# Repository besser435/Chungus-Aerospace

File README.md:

# Chungus-Aerospace
For the model rockets made by my friend and myself.
Most of the code was written before I knew how to code/keep it maintainable, which is why pretty much everything is terrible.

chung

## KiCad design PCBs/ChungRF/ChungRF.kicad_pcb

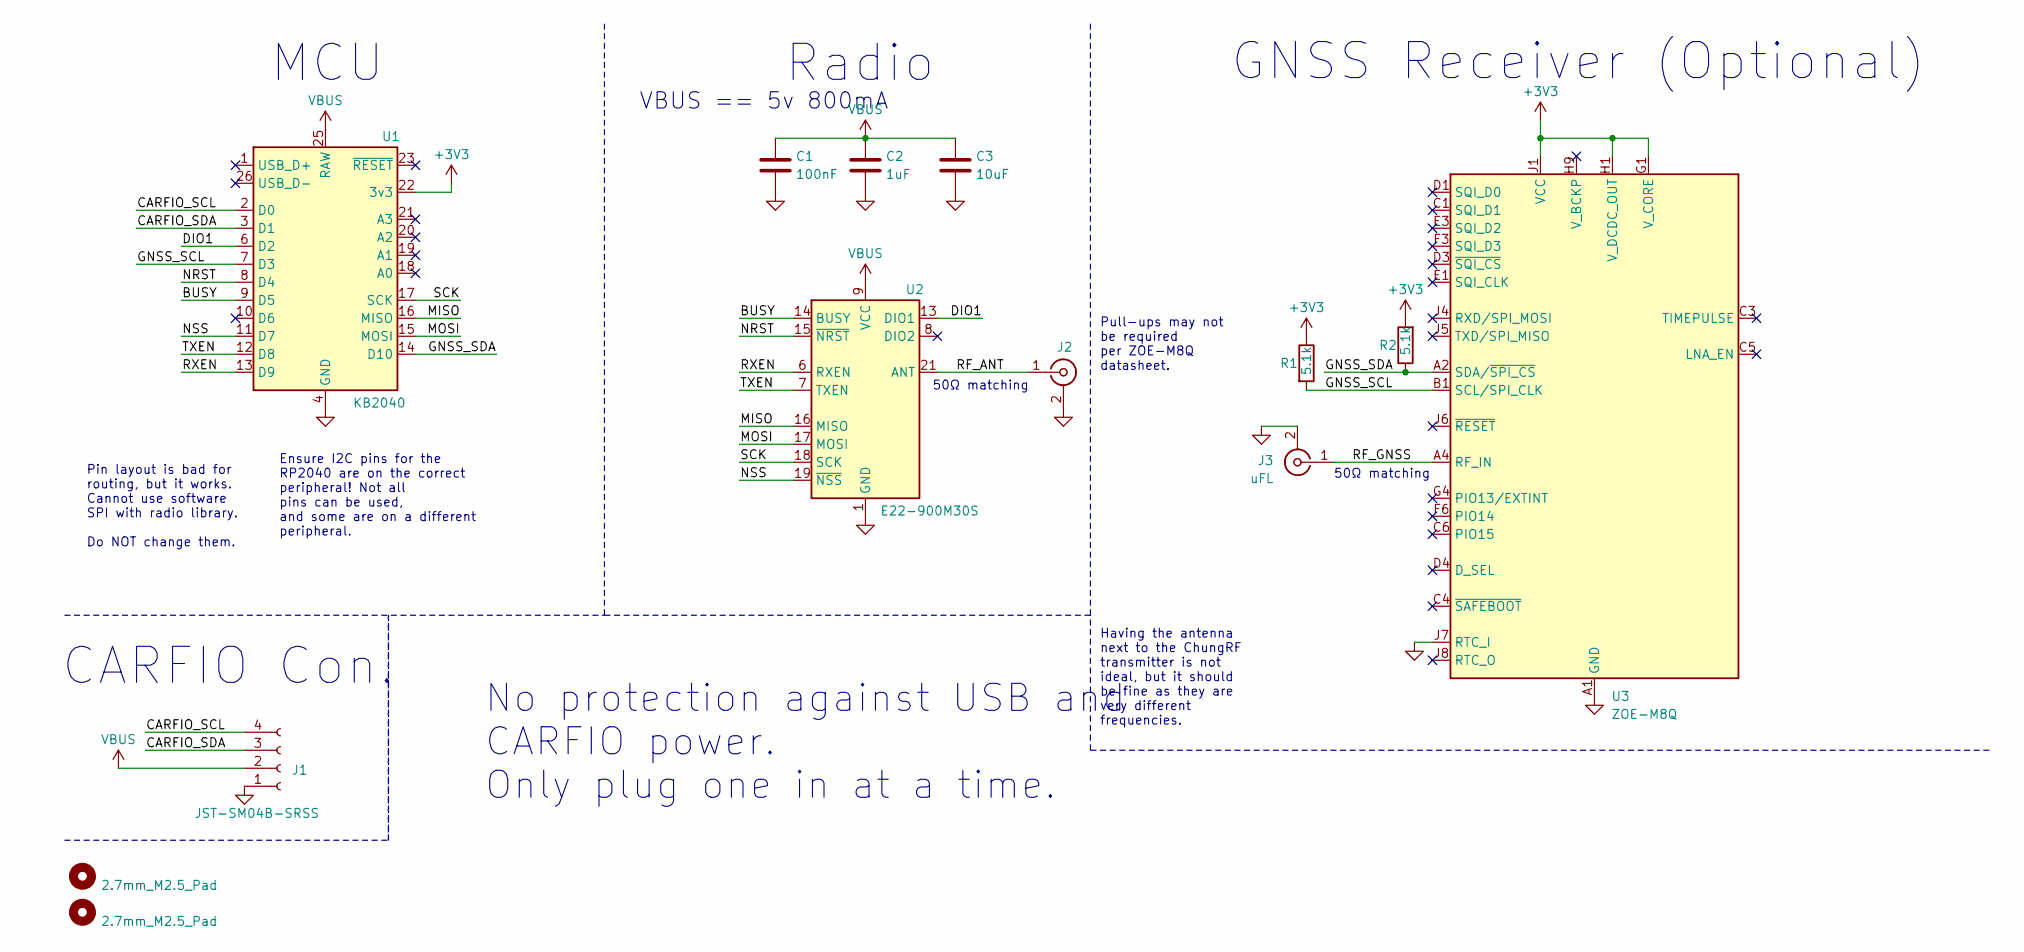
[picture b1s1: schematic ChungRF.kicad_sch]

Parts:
C1: 100nF; C_0603_1608Metric
C2: 1uF; C_0603_1608Metric
C3: 10uF; C_0603_1608Metric
H1, H2: 2.7mm_M2.5_Pad; M2.5_2.7mm_hole
J1: JST-SM04B-SRSS; JST_SH_SM04B-SRSS-TB_1x04-1MP_P1.00mm_Horizontal
J2: Conn_Coaxial; CONSMA003.062
J3: uFL; U.FL_Hirose_U.FL-R-SMT-1_Vertical
R1, R2: 5.1k; C_0603_1608Metric
U1: KB2040; Adafuit-KB2040-SMD
U2: E22-900M30S
U3: ZOE-M8Q; ublox_ZOE_M8

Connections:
+3V3: R1.1, R2.2, U1.22 (3v3), U3.G1 (V_CORE), U3.H1 (V_DCDC_OUT), U3.J1 (VCC), U3.J2 (VCC)
/BUSY: U1.9 (D5), U2.14 (BUSY)
/CARFIO_SCL: J1.4, U1.2 (D0)
/CARFIO_SDA: J1.3, U1.3 (D1)
/DIO1: U1.6 (D2), U2.13 (DIO1)
/GNSS_SCL: R1.2, U1.7 (D3), U3.B1 (SCL/SPI_CLK)
/GNSS_SDA: R2.1, U1.14 (D10), U3.A2 (SDA/~SPI_CS)
/MISO: U1.16 (MISO), U2.16 (MISO)
/MOSI: U1.15 (MOSI), U2.17 (MOSI)
/NRST: U1.8 (D4), U2.15 (~NRST)
/NSS: U1.11 (D7), U2.19 (~NSS)
/RF_ANT: J2.1 (In), U2.21 (ANT)
/RF_GNSS: J3.1 (In), U3.A4 (RF_IN)
/RXEN: U1.13 (D9), U2.6 (RXEN)
/SCK: U1.17 (SCK), U2.18 (SCK)
/TXEN: U1.12 (D8), U2.7 (TXEN)
GND: C1.2, C2.2, C3.2, J1.1, J2.2 (Ext), J3.2 (Ext), U1.4 (GND), U1.5 (GND), U1.24 (GND), U2.1 (GND), U2.2 (GND), U2.3 (GND), U2.4 (GND), U2.5 (GND), U2.11 (GND), U2.12 (GND), U2.20 (GND), U2.22 (GND), U3.A1 (GND), U3.A3 (GND), U3.A5 (GND), U3.A7 (GND), U3.A8 (GND), U3.A9 (GND), U3.B9 (GND), U3.C7 (GND), U3.C9 (GND), U3.D6 (GND), U3.D9 (GND), U3.E7 (GND), U3.F7 (GND), U3.G3 (GND), U3.G6 (GND), U3.G7 (GND), U3.J3 (GND), U3.J7 (RTC_I), U3.J9 (GND)
VBUS: C1.1, C2.1, C3.1, J1.2, U1.25 (RAW), U2.9 (VCC), U2.10 (VCC)

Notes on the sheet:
VBUS == 5v 800mA
Radio
No protection against USB and CARFIO power. Only plug one in at a time.
Having the antenna next to the ChungRF transmitter is not ideal, but it should be fine as they are very different frequencies.
MCU
CARFIO Con.
Pull-ups may not be required per ZOE-M8Q datasheet.
Ensure I2C pins for the RP2040 are on the correct peripheral! Not all pins can be used, and some are on a different peripheral.
Pin layout is bad for routing, but it works. Cannot use software SPI with radio library. Do NOT change them.
50Ω matching
GNSS Receiver (Optional)

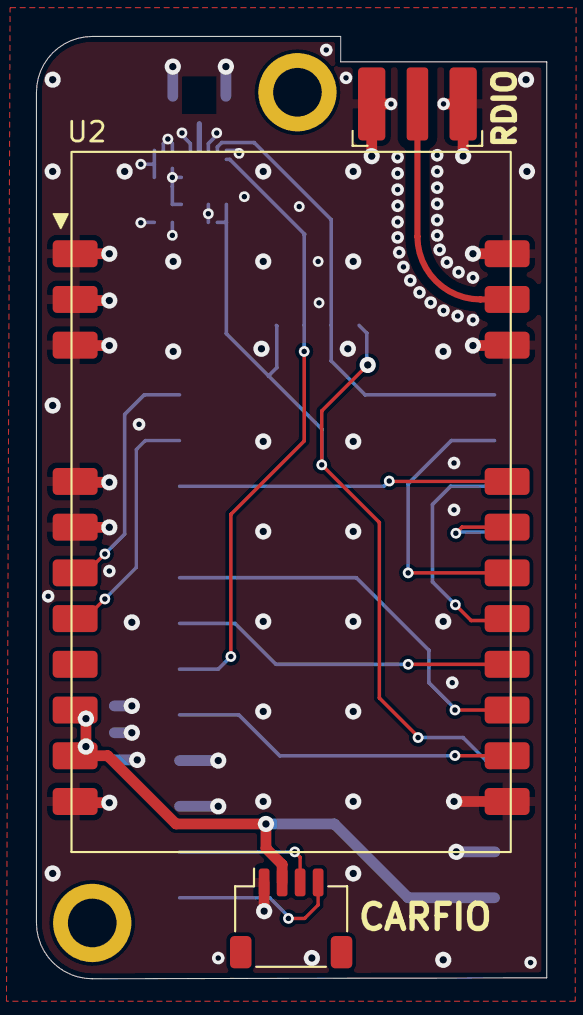
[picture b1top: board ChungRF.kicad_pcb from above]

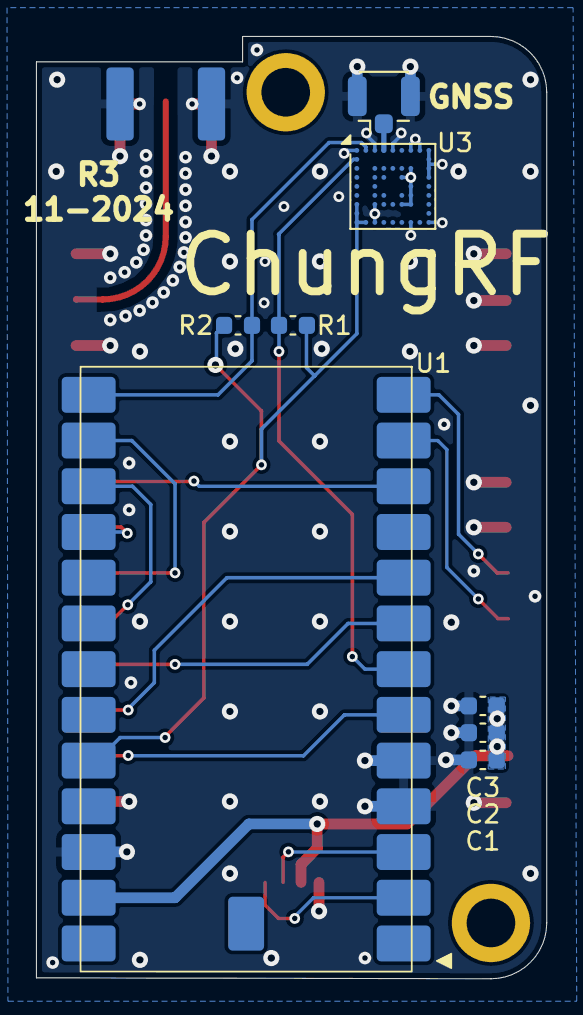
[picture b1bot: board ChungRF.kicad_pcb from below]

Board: 4 copper layers, 28.3 x 52.3 mm, 13 parts (8 on the bottom side), 18 nets.

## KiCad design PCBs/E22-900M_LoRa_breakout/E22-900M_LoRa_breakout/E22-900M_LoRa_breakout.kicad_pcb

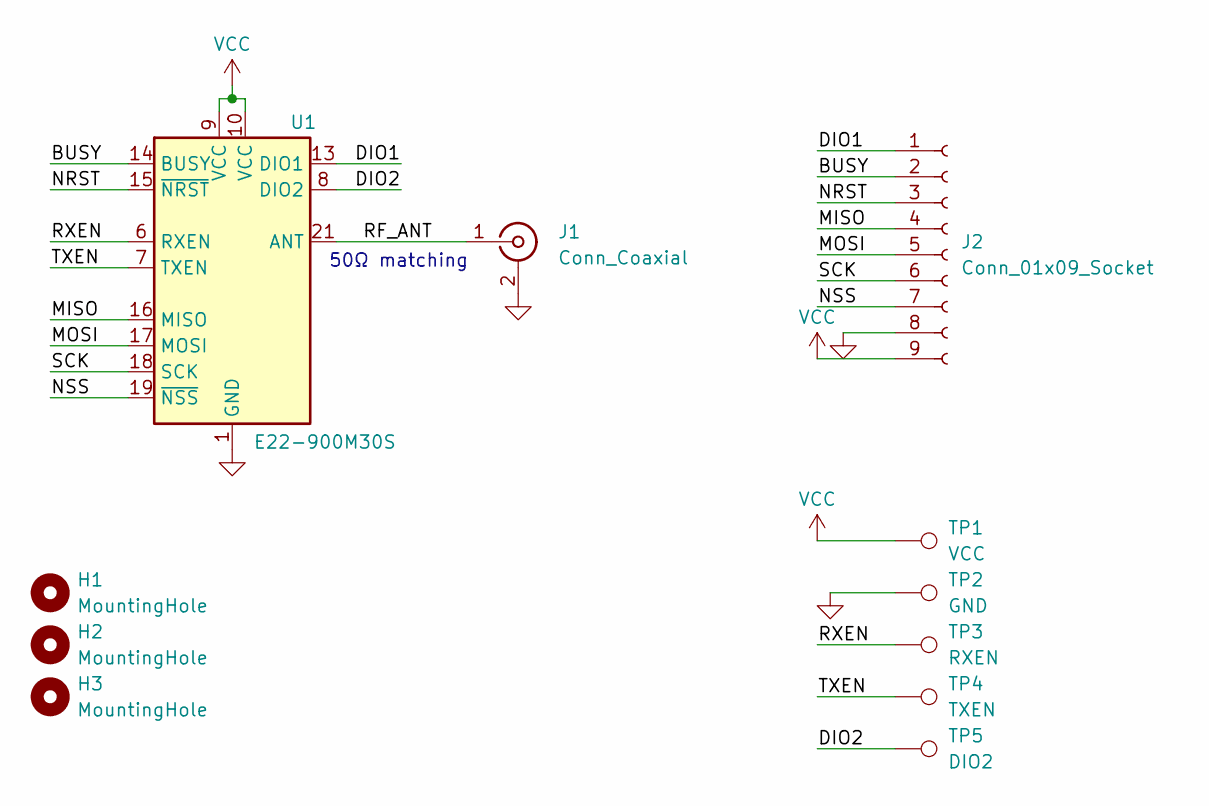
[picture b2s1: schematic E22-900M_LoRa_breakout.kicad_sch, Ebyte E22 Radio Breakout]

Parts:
H1, H2, H3: MountingHole; MountingHole_2.7mm_M2.5_Pad_Via
J1: Conn_Coaxial; CON-SMA-EDGE-S
J2: Conn_01x09_Socket; JST_GH_BM09B-GHS-TBT_1x09-1MP_P1.25mm_Vertical
TP1: VCC; TestPoint_Pad_D1.5mm
TP2: GND; TestPoint_Pad_D1.5mm
TP3: RXEN; TestPoint_Pad_D1.5mm
TP4: TXEN; TestPoint_Pad_D1.5mm
TP5: DIO2; TestPoint_Pad_D1.5mm
U1: E22-900M30S

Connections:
/BUSY: J2.2, U1.14 (BUSY)
/DIO1: J2.1, U1.13 (DIO1)
/DIO2: TP5.1, U1.8 (DIO2)
/MISO: J2.4, U1.16 (MISO)
/MOSI: J2.5, U1.17 (MOSI)
/NRST: J2.3, U1.15 (~NRST)
/NSS: J2.7, U1.19 (~NSS)
/RF_ANT: J1.1 (In), U1.21 (ANT)
/RXEN: TP3.1, U1.6 (RXEN)
/SCK: J2.6, U1.18 (SCK)
/TXEN: TP4.1, U1.7 (TXEN)
GND: J1.2 (Ext), J2.8, TP2.1, U1.1 (GND), U1.2 (GND), U1.3 (GND), U1.4 (GND), U1.5 (GND), U1.11 (GND), U1.12 (GND), U1.20 (GND), U1.22 (GND)
VCC: J2.9, TP1.1, U1.9 (VCC), U1.10 (VCC)

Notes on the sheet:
50Ω matching

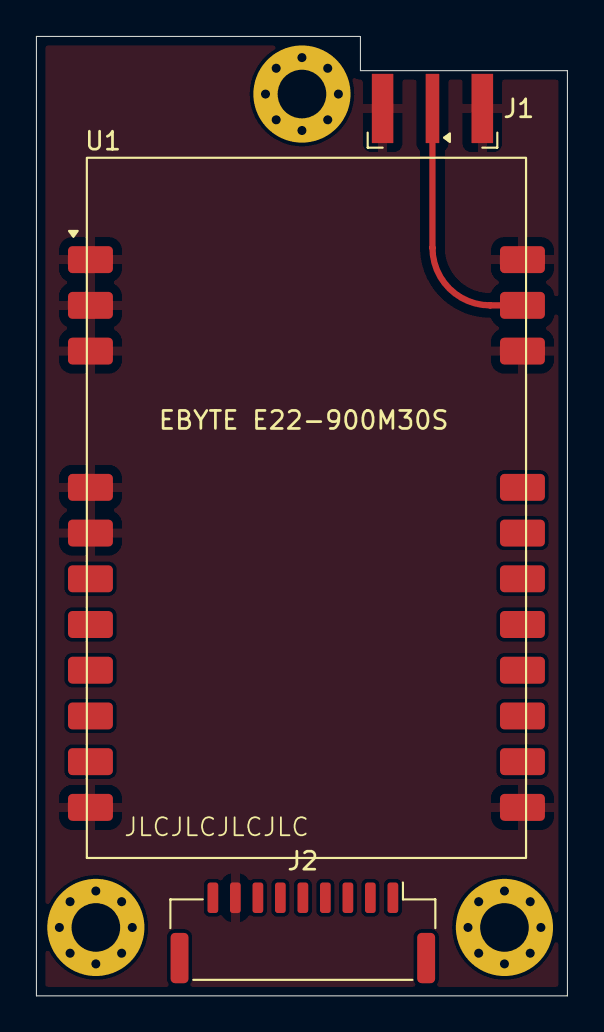
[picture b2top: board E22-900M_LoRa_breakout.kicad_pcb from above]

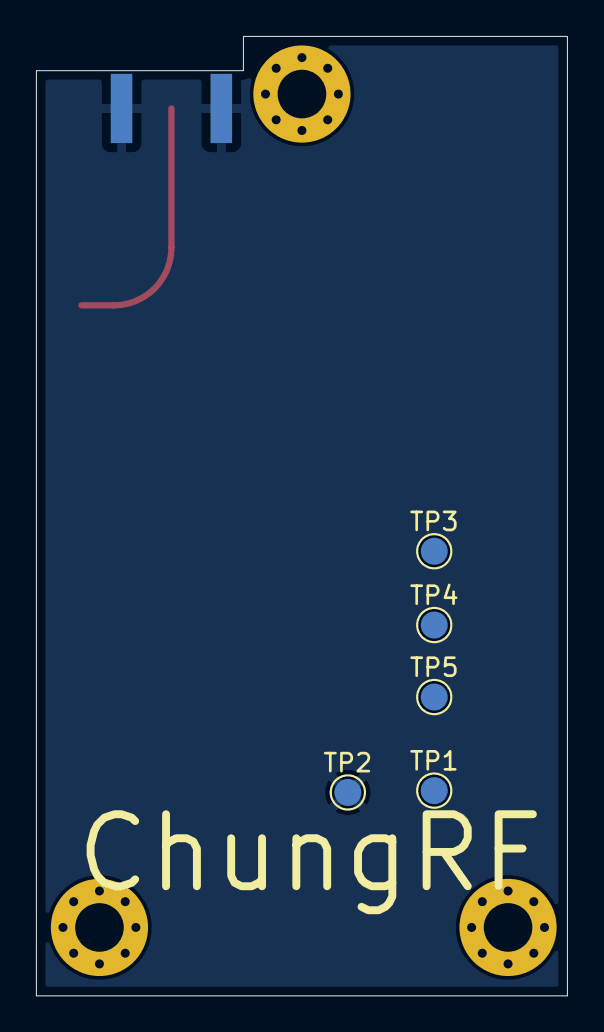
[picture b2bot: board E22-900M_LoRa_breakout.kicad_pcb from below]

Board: 4 copper layers, 29.5 x 53.3 mm, 11 parts (5 on the bottom side), 13 nets.

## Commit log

2021-12-29 chung
2021-12-29 v0.1
2021-12-31 v0.2
2021-12-31 borrowed project
    Hippity hoppity your code is now my property
2022-01-05 v0.2.1
    Added possible chute deploy code
2022-01-06 Added Feather Libraries
2022-01-06 v0.2.3
2022-01-08 v1.0
2022-01-09 v1.0.1
2022-01-12 v1.1
    debunged a few things
2022-01-12 legacy code
    This used to be required, but we changed how the code works. Because of this we don't need this bit anymore. I'm just uploading it incase we do need it again for whatever reason. We didn't write this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
2022-01-12 moved files
2022-01-12 Delete Feather-M4 Flight Telemetry Software.py
    Renamed to code.py so its easier to work with on the Feather.
2022-01-12 v1.2
2022-01-12 moved
2022-01-12 v1.3
2022-01-13 v1.1.1
2022-01-13 Our flight logs go here
2022-01-14 v1.1
2022-01-14 v1.4
2022-01-15 v1.5
2022-01-15 v0.1.1
2022-01-15 Why did I even make this
2022-01-16 1-15-22
2022-01-19 ooga booga
2022-01-19 v0.1.2
2022-01-19 test
2022-01-20 Committed to wrong part
2022-01-20 Name changes
2022-01-20 did the thing again
2022-01-20 File name change
2022-01-20 Updating files
2022-01-20 Clarified file names
2022-01-20 v1.6
2022-01-20 v0.1.3
2022-01-21 debugging logs for logging issue
2022-01-21 v1.7
2022-01-24 v1.8
2022-01-25 v1.8.1
2022-01-25 Updated directory structure
2022-01-25 Create why
2022-01-26 v1.9
2022-02-02 v2.2-alpha.1
2022-02-03 v2.0-alpha.2.3
    File and version name changes
2022-02-06 Adding untested MPIM parts
    Gotta make sure all the parts work together before committing to the main branch. Maybe even an operational flight.
2022-02-08 v1.10
2022-02-08 I will not make this a pull request
2022-02-09 Redoing RUD
2022-02-09 v2.0-alpha.3
2022-02-12 Updated tolerances a little
    It was wiggling around a little bit, so I made the tolerances a bit tighter to hopefully fix that.
2022-02-12 this part sucks lol
2022-02-16 v2.0-alpha.4
2022-02-17 CALC v2.0-alpha.5
2022-02-17 v1.10.2
2022-02-17 add CALCv1 mounts
2022-02-23 v1.11
2022-03-04 v2.0-alpha.6
2022-03-05 Moved MPIM stuff around, added 49mm MPIM
2022-03-14 v2.0-beta.1
2022-03-17 v1.12
2022-03-20 v2.0-beta.2
2022-03-22 v2.0-beta.3
2022-03-29 Not needed anymore
2022-04-06 v1.13
2022-04-06 v1.1.2
2022-04-08 v2.0-beta.4
2022-04-28 4-27-22
2022-05-04 init
2022-05-05 v2.0-beta.5
2022-05-15 More dual deployment parts
    Added a small 37.6x60mm avionics bay, bulkhead/coupler with space for wires and a pyro charge, 50mm long body tube for drogueless dual deployment, and a motor mount part that I forgot to add a while 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
2022-06-18 Transition to flyaway rod guide
    24x70mm only though, the 18mm ones are obsolete anyway
2022-07-05 updated lib
2022-07-06 flight
2022-07-14 Challenger ejection charge software v0.1
2022-07-21 First set of Full Send parts
2022-07-28 debung
2022-07-30 v1.2.1
2022-08-02 Updated Full Send
2022-08-20 v2.0-beta.6
2022-09-08 v1.14
2022-11-13 QT py velocity v0
    Now takes 30 seconds to reach FTL speeds instead of 3
    Also organized the clusterfuck of a QT py folder
2022-11-14 v1.1
    Made the code a bit neater
2022-11-14 v1.1 (#7)
    Made the code a bit neater
2022-11-20 Made integral less stupid
    Still untested, could very well be totally fucked, but it's definitely better than before
2022-11-20 Made variables less stupid and more readable
2022-11-21 defuck (#8)
    * Made integral less stupid
    * Made variables less stupid and more readable
2022-12-16 Fuller Send aerostructure
    .stl files and .csv file for the nose cone
2022-12-19 moved CALCv2
2022-12-25 v1.15-alpha.1
2022-12-25 Removed useless files
2022-12-25 Create code.py
    (Still untested, apparently I'm supposed to spend time with my family or something)
2022-12-30 Full accelerometer calibration, velocity logging
    I hate this
2022-12-31 Accelerometer calibration (#10)
    * Create code.py
    (Still untested, apparently I'm supposed to spend time with my family or something)
    * Full accelerometer calibration, velocity logging
    I hate this
    * Update code.py
    * Update code.py
2022-12-31 update file structure
2022-12-31 v1.15-beta.1
2022-12-31 v1.15
2023-01-03 v1.0-alpha.1
2023-03-01 Create Autism Ray PCB
2023-03-02 Update PCB
2023-03-02 Before ground pour
2023-03-02 Actaully before ground pour
2023-03-02 Actually after ground pour
2023-03-02 Update gitignore
2023-03-04 Update Eagle libraries
2023-03-09 Added XIAO lib
2023-03-15 Autosaves
2023-03-16 TF2 autosave
2023-03-17 Yagi hardware + calibration slight defuck
2023-03-19 Create thick parts
2023-03-19 v2.0-beta.7
2023-03-25 Tax Fraud v2 PCB
2023-03-25 Update autism_ray_xaio.b##
2023-04-12 Create TVC logic.py
    Needs more work. Idk how to reference specific elements in the array yet, but it's a start.
2023-04-13 TVC logic quat normalization + Euler
    Hopefully added code for normalizing the quaternion, and calculating one of the Euler angles. It should be possible to do a sanity check with this.
2023-04-14 TVC Euler math
    Finished Euler angle conversion math
2023-04-29 v1.0.2
    Rename to avoid linting errors in VS Code
2023-05-10 v1.0.3
2023-05-13 2020 rail/38mm launch tower parts
2023-05-14 Create BasicKalmanTest.py
    File for Kalman filter testing, no idea if it'll work
2023-05-28 v.1.1
2023-06-06 FS2 Avbay
2023-06-07 FS2 full avbay assembly
2023-06-08 FS2 avbay tolerance fix
    Defucked OD from 38.6mm to 38mm
2023-06-09 FS2 motor block
2023-06-29 FS2 motor blovck defuck i think
    I changed something maybe a week ago and forgot to commit lol
2023-06-29 FS2 29mm adapter
2023-07-01 TVC configuration
    something something conflicted file idk seems fine to me
2023-07-01 TVC configuration defuck
2023-07-02 Improved calibration
    Print formatting, gyro calibration, range defuck, renamed variables, kalman filter test that I completely forgot about
2023-07-02 stupid fucking radian conversion + format defuck
2023-07-06 7-6-23 launch
2023-07-11 Accelerometer velocity potential defuck
    Created cfg setup and new velocity logic that integrates first before getting the magnitude of the velocity vector.
2023-07-24 TVC logic setup (#11)
    * Create TVC logic.py
    Needs more work. Idk how to reference specific elements in the array yet, but it's a start.
    * TVC logic quat normalization + Euler
    Hopefully added code for normalizing the quaternion, and calculating one of the Euler angles. It should be possible to do a sanity check with this.
    * TVC Euler math
    Finished Euler angle conversion math
2023-07-24 TVC changes
2023-07-25 TVC array error possible defuck #2
2023-07-28 TVC/Accel logic defuck #3 (final)
    Modified TVC logic so it actually fucking works, cleaned it up and added comments so it's more readable, improved calibration, added PID constants to TVC config file for use in future features
2023-08-07 TVC body tube + nose cone generator
2023-09-15 TVC rocket body + QoL changes
    Updated TVC rocket body, changed frequency formula for autism ray ground software, unfucked nose cone generator math
2023-10-27 Rename, start landed function
2023-10-27 v1.3
    Add exit() in while True loop under keyboardInterrupt, fix HB text cutoff
2023-12-21 Remove old stuff
2024-01-26 v1.4: add display info, add cron job comment
2024-01-30 chunglib tvc 1
2024-01-30 FS2/TVC defuck?????
2024-01-30 chunglib tvc 1 (#12)
2024-02-03 Add UART test stuff
2024-02-07 Add initial AR2 tests
2024-02-14 Rev B - Fix UART pins
2024-02-14 Rev B - Improve ground plane
2024-02-14 Continue work on AR2
2024-02-16 git commit in case sussy house fire
    I am scared of data loss okay
2024-02-20 Update AR2 stuff
2024-02-23 AR2 updates
2024-03-04 Update AR2
2024-03-05 I am going insane
2024-03-07 Change out stupid fucking display library for an amazing one
2024-03-08 Update AR2, mostly functional now
2024-03-09 Change boot behavior, add alert display function
2024-03-20 Change fix quality to 3D indicator
2024-03-26 Blink on send to save power, add/fix comments
2024-04-04 Add power saving features, start on proper logging
2024-04-06 v1.2 - Reduce power by ~20mA
2024-04-06 v1.2.1 - Further reduce power draw
2024-05-15 Some software changes
2024-05-15 Create ChungRF
2024-05-15 Rename to ChungRF
2024-05-17 Update ChungRF
2024-05-20 Fix impedance
2024-05-24 Finalize design, add gerbers
2024-06-12 Update ChungRF, add software tests
2024-06-25 Last R1
2024-06-25 Add ESP32-S3-MINI
2024-06-28 ChungRF R2
2024-07-17 Add ChungRF tests
2024-07-17 Add MP SX126x lib (doesnt work)
2024-07-23 Update ChungRF tests
2024-10-07 turn good_sound into a class
2024-10-10 Add stop function, make second pin optional
2024-10-21 Fix ChungRF software
2024-10-21 ChungRF R3
2024-10-25 Clean Tracks, add Gerber files
2024-11-14 ChungRF R4 - Fix GNSS I2C bus
2024-11-14 Reorganize ChungRF stuff confirm the radios work
2024-11-27 Clean up stuff
2025-03-19 change some minor things
2025-03-19 Change to continuous listening (make it actually work)
